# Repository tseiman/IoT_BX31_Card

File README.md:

# IoT BX31 Card

IoT card for Sierra Wireless MangOH (https://mangoh.io) boards.
Connects the Sierra Wirelss  BX3105 Module via UART to the (WP) Module.
The IoT card is easy to use by using the Legato (https://legato.io) AT command interpreter.

## Programming the EEPROM
After hardware production the EEPROM needs to be one time flashed with the Identity and configuration data of the IoT card.
Please see the eeprom folder for further information. 

## Basic testing on MangOH
Ensure that the UART of the WP module is configured correctly to handle the IoT module - e.g. by configuring it via `AT!MAPUART=17,1` command on the WP module (please cross check the WP AT User guide).
**Ensure that the GPIO's are set correctly**. On MangOH red this are GPIO 42 for Firmware update and GPIO 2 for enable. The BX31 IoT module supports update of the Firmware over UART by pulling GPIO 42 low (it is a Active Low Pin on BX3105). For normal operation **pull GPIO42 high (important)**. To reset the card you need to pull "enable" GPIO 2  High and then pull it down again - so the BX3105 gets enabled.

Disable Firmware update GPIO from command line:
```
~# echo 42 >/sys/class/gpio/export
~# echo out >/sys/class/gpio/gpio42/direction
~# echo 0 > /sys/class/gpio/gpio42/value
```
Reset the Module:
```
~# echo 2 >/sys/class/gpio/export
~# echo out >/sys/class/gpio/gpio2/direction
~# echo 1 > /sys/class/gpio/gpio2/value
~# echo 0 > /sys/class/gpio/gpio2/value
```

Now you can connect to the UART by using microcom and it should react to BX31 AT commands:
```
~# microcom -X -s 115200 /dev/ttyHS0
ATI

BX3105

OK
```
You can exit microcom by pressing **CTRL-X**. Please remember that when typing AT commands you'll not see what you type becasue BX31 are not echoing back. 

You can also read the content of the IoT card EEPROM, by reading it over I2C with i2cdump:

```
TBD
```

## Using it the IoT card in Legato

Ensure the UART of the WP module is configured in the right way. On a WP76 this can be done with the `AT!MAPUART=17,1` command. 
For further Information check the AT command guide of the Module you plan to use. 
The IoT module will be then accessible over the `/dev/ttyHS0` UART in Legato.
You might do this setoup out of a Legato application by using the Legato AT interpreter API.

In case you plan to use the BX31 IoT module in an Legato environment and to control it from a Legato Application - ensure that you have read/write access to the device.
This can be configured in the **requires - devices** section of your Legato appliactions **.adef** file - e.g.:

```
requires:
{
    device:
    {
       [rw]    /dev/ttyHS0    /dev/ttyHS0
    }
}

```

Ensure in the same file that you bind the AT Interpreter API to your project:

```
bindings:
{
    bx31_atservice.BX31_ATServiceComponent.le_atClient -> atService.le_atClient
...    
}
```

Now you can use the API to control the BX31 IoT Board - see this snippeds as some example (more glue code might be needed):

```c
        fd = le_tty_Open(BX31_SERIAL_DEVICE, O_RDWR | O_NDELAY | O_NOCTTY | O_NONBLOCK); // opening the UART2 - which is connected to the IoT Board
        if (fd == -1) {
                LE_ERROR("failed to open UART device");
                exit(EXIT_FAILURE);
        }
        
       ...

        LE_ASSERT(le_tty_SetBaudRate(fd, LE_TTY_SPEED_115200) == LE_OK);        // assuming BX31 is on 115200
        LE_ASSERT(le_tty_SetFraming(fd, 'N', 8, 1) == LE_OK);                   // set UART framing to 8bit, No Parity, 1 Stop bit
        LE_ASSERT(le_tty_SetRaw(fd, 10, 30000) == LE_OK);                       // We need raw UART mode (the canonical echo's
                                                                                // back to peer)
       ...

        DevRef = le_atClient_Start(fd);

        cmdRef = le_atClient_Create();                                          // instantiate an AT interpreter client

        /* --- check if we're really talking to BX31 --- */
        LE_INFO("Check BX310x presence");                                       // We ask for device identification string

        LE_ASSERT(le_atClient_SetCommandAndSend
                  (&cmdRef, DevRef, "ATI", "", "OK|ERROR|+CME ERROR",
                   LE_ATDEFS_COMMAND_DEFAULT_TIMEOUT) == LE_OK);

        LE_ASSERT(le_atClient_GetFinalResponse
                  (cmdRef, buffer, LE_ATDEFS_RESPONSE_MAX_BYTES) == LE_OK);

        memset(buffer, 0, 50);

        LE_ASSERT(le_atClient_GetFirstIntermediateResponse
                  (cmdRef, buffer, LE_ATDEFS_RESPONSE_MAX_BYTES) == LE_OK);

        if (strncmp(buffer, "BX310", 4) != 0) {                                 // and compare it with the expected
                LE_ERROR("This doesn seem to be a BX310x bluetooth module, "
                                "exiting. Response was \"%s\"", buffer);        // if the BT module is not answering we better exit

      ...

        LE_INFO("Disable WiFi on BX310x");                                      // here we use the BX just for BT scanning
        LE_ASSERT(le_atClient_SetCommandAndSend
                  (&cmdRef, DevRef, "AT+SRWCFG=0", "", "OK|ERROR|+CME ERROR",
                   LE_ATDEFS_COMMAND_DEFAULT_TIMEOUT) == LE_OK);

``` 

For further information please check the legato AT API https://docs.legato.io/17_09/c_atClient.html
There is also a project related to this IoT Board which is used to do a bluetooth scanning: 
https://github.com/tseiman/SWILegatoBTScanner_BX31_AVS

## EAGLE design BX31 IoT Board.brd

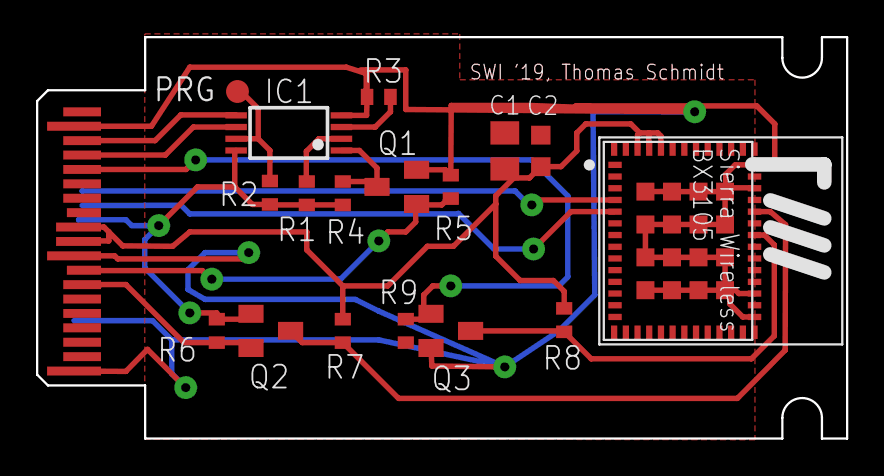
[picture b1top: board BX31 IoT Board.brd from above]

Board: 2 copper layers, 45.0 x 22.3 mm, 18 parts (0 on the bottom side), 16 nets.

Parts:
C1: 22u; C0805K
C2: C0603K
IC1: CAT24C32 YI-GT3; TSSOP8
MODULE1: BX3105
PRG: TPSB1,27; B1,27
Q1, Q2, Q3: BSS138; SOT23
R1, R2, R3, R4, R5, R6, R7, R8, R9: 10k; R0402
U$1: IOT

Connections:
BX-RX_IOT-TX: MODULE1.5, U$1.12
BX-TX_IOT-RX: MODULE1.4, U$1.13
EEPROM_A0: IC1.1, Q1.3, R4.1
EEPROM_A1: IC1.2, R1.1
EEPROM_A2: IC1.3, R3.2
EEPROM_WP: IC1.7, PRG.TP, R2.1
ENABLE: MODULE1.37, Q2.3, R7.1
FW_UPDATE: MODULE1.35, Q3.3, R8.1
GND: C1.2, C2.2, IC1.4, MODULE1.28, MODULE1.30, MODULE1.39, MODULE1.41, MODULE1.G1, MODULE1.G2, MODULE1.G3, MODULE1.G4, MODULE1.G5, MODULE1.G6, MODULE1.G7, MODULE1.G8, MODULE1.G9, MODULE1.G10, MODULE1.G11, MODULE1.G12, MODULE1.G13, MODULE1.G14, MODULE1.G15, MODULE1.G16, Q1.2, Q3.2, R3.1, R5.1, R9.2, U$1.4, U$1.21, U$1.30, U$1.38
GPIO_1_1V8: Q3.1, R9.1, U$1.24
I2C_SCL: IC1.6, U$1.23
I2C_SDA: IC1.5, U$1.22
N_CARD_DETECT: Q1.1, R5.2, U$1.31
N_RESET: Q2.2, R6.1, U$1.32
VCC_1V8: IC1.8, Q2.1, R1.2, R2.2, R4.2, R6.2, U$1.11
VCC_3V3: C1.1, C2.1, MODULE1.50, MODULE1.51, MODULE1.52, R7.2, R8.2, U$1.28, U$1.29

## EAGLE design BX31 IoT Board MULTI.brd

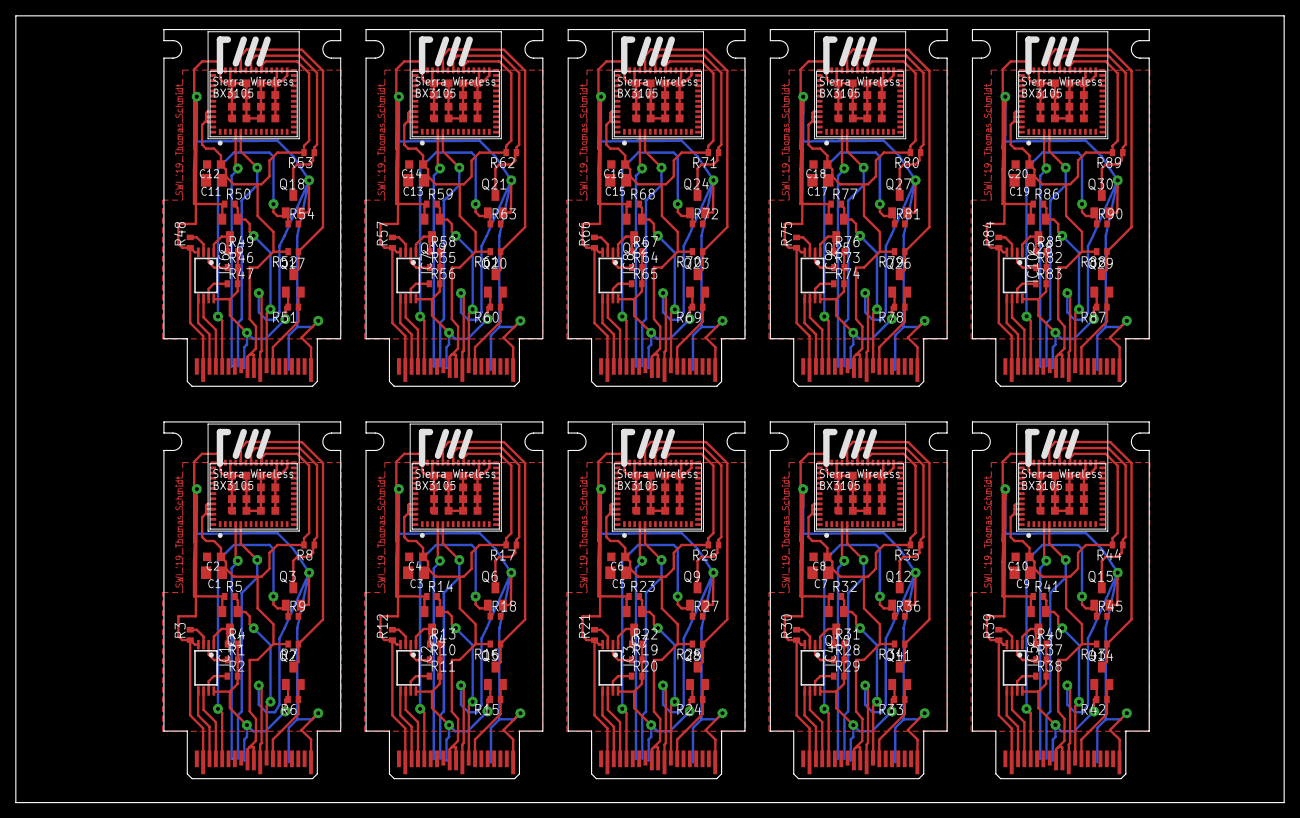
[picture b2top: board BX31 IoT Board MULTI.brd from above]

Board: 2 copper layers, 160.0 x 99.2 mm, 170 parts (0 on the bottom side), 160 nets.

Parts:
C1, C3, C5, C7, C9, C11, C13, C15, C17, C19: 22u; C0805K
C2, C4, C6, C8, C10, C12, C14, C16, C18, C20: C0603K
IC1, IC2, IC3, IC4, IC5, IC6, IC7, IC8, IC9, IC10: CAT24C32 YI-GT3; TSSOP8
MODULE1, MODULE2, MODULE3, MODULE4, MODULE5, MODULE6, MODULE7, MODULE8, MODULE9, MODULE10: BX3105
Q1, Q2, Q3, Q4, Q5, Q6, Q7, Q8, Q9, Q10, Q11, Q12, Q13, Q14, Q15, Q16, Q17, Q18, Q19, Q20, Q21, Q22, Q23, Q24, Q25, Q26, Q27, Q28, Q29, Q30: BSS138; SOT23
R1, R2, R3, R4, R5, R6, R7, R8, R9, R10, R11, R12, R13, R14, R15, R16, R17, R18, R19, R20, R21, R22, R23, R24, R25, R26, R27, R28, R29, R30, R31, R32, R33, R34, R35, R36, R37, R38, R39, R40, R41, R42, R43, R44, R45, R46, R47, R48, R49, R50, R51, R52, R53, R54, R55, R56, R57, R58, R59, R60, R61, R62, R63, R64, R65, R66, R67, R68, R69, R70, R71, R72, R73, R74, R75, R76, R77, R78, R79, R80, R81, R82, R83, R84, R85, R86, R87, R88, R89, R90: 10k; R0402
U$1, U$2, U$3, U$4, U$5, U$6, U$7, U$8, U$9, U$10: IOT

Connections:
BX-RX_IOT-TX: MODULE1.5, U$1.12
BX-RX_IOT-TX1: MODULE2.5, U$2.12
BX-RX_IOT-TX2: MODULE3.5, U$3.12
BX-RX_IOT-TX3: MODULE4.5, U$4.12
BX-RX_IOT-TX4: MODULE5.5, U$5.12
BX-RX_IOT-TX5: MODULE6.5, U$6.12
BX-RX_IOT-TX6: MODULE7.5, U$7.12
BX-RX_IOT-TX7: MODULE8.5, U$8.12
BX-RX_IOT-TX8: MODULE9.5, U$9.12
BX-RX_IOT-TX9: MODULE10.5, U$10.12
BX-TX_IOT-RX: MODULE1.4, U$1.13
BX-TX_IOT-RX1: MODULE2.4, U$2.13
BX-TX_IOT-RX2: MODULE3.4, U$3.13
BX-TX_IOT-RX3: MODULE4.4, U$4.13
BX-TX_IOT-RX4: MODULE5.4, U$5.13
BX-TX_IOT-RX5: MODULE6.4, U$6.13
BX-TX_IOT-RX6: MODULE7.4, U$7.13
BX-TX_IOT-RX7: MODULE8.4, U$8.13
BX-TX_IOT-RX8: MODULE9.4, U$9.13
BX-TX_IOT-RX9: MODULE10.4, U$10.13
EEPROM_A0: IC1.1, Q1.3, R4.1
EEPROM_A1: IC1.2, R1.1
EEPROM_A2: IC1.3, R3.2
EEPROM_A3: IC2.3, R12.2
EEPROM_A4: IC2.2, R10.1
EEPROM_A5: IC2.1, Q4.3, R13.1
EEPROM_A6: IC3.3, R21.2
EEPROM_A7: IC3.2, R19.1
EEPROM_A8: IC3.1, Q7.3, R22.1
EEPROM_A9: IC4.3, R30.2
EEPROM_A10: IC4.2, R28.1
EEPROM_A11: IC4.1, Q10.3, R31.1
EEPROM_A12: IC5.3, R39.2
EEPROM_A13: IC5.2, R37.1
EEPROM_A14: IC5.1, Q13.3, R40.1
EEPROM_A15: IC6.3, R48.2
EEPROM_A16: IC6.2, R46.1
EEPROM_A17: IC6.1, Q16.3, R49.1
EEPROM_A18: IC7.3, R57.2
EEPROM_A19: IC7.2, R55.1
EEPROM_A20: IC7.1, Q19.3, R58.1
EEPROM_A21: IC8.3, R66.2
EEPROM_A22: IC8.2, R64.1
EEPROM_A23: IC8.1, Q22.3, R67.1
EEPROM_A24: IC9.3, R75.2
EEPROM_A25: IC9.2, R73.1
EEPROM_A26: IC9.1, Q25.3, R76.1
EEPROM_A27: IC10.3, R84.2
EEPROM_A28: IC10.2, R82.1
EEPROM_A29: IC10.1, Q28.3, R85.1
EEPROM_WP: IC1.7, R2.1
EEPROM_WP1: IC2.7, R11.1
EEPROM_WP2: IC3.7, R20.1
EEPROM_WP3: IC4.7, R29.1
EEPROM_WP4: IC5.7, R38.1
EEPROM_WP5: IC6.7, R47.1
EEPROM_WP6: IC7.7, R56.1
EEPROM_WP7: IC8.7, R65.1
EEPROM_WP8: IC9.7, R74.1
EEPROM_WP9: IC10.7, R83.1
ENABLE: MODULE1.37, Q2.3, R7.1
ENABLE1: MODULE2.37, Q5.3, R16.1
ENABLE2: MODULE3.37, Q8.3, R25.1
ENABLE3: MODULE4.37, Q11.3, R34.1
ENABLE4: MODULE5.37, Q14.3, R43.1
ENABLE5: MODULE6.37, Q17.3, R52.1
ENABLE6: MODULE7.37, Q20.3, R61.1
ENABLE7: MODULE8.37, Q23.3, R70.1
ENABLE8: MODULE9.37, Q26.3, R79.1
ENABLE9: MODULE10.37, Q29.3, R88.1
FW_UPDATE: MODULE1.35, Q3.3, R8.1
FW_UPDATE1: MODULE2.35, Q6.3, R17.1
FW_UPDATE2: MODULE3.35, Q9.3, R26.1
FW_UPDATE3: MODULE4.35, Q12.3, R35.1
FW_UPDATE4: MODULE5.35, Q15.3, R44.1
FW_UPDATE5: MODULE6.35, Q18.3, R53.1
FW_UPDATE6: MODULE7.35, Q21.3, R62.1
FW_UPDATE7: MODULE8.35, Q24.3, R71.1
FW_UPDATE8: MODULE9.35, Q27.3, R80.1
FW_UPDATE9: MODULE10.35, Q30.3, R89.1
GND: C1.2, C2.2, IC1.4, MODULE1.28, MODULE1.30, MODULE1.39, MODULE1.41, MODULE1.G1, MODULE1.G2, MODULE1.G3, MODULE1.G4, MODULE1.G5, MODULE1.G6, MODULE1.G7, MODULE1.G8, MODULE1.G9, MODULE1.G10, MODULE1.G11, MODULE1.G12, MODULE1.G13, MODULE1.G14, MODULE1.G15, MODULE1.G16, Q1.2, Q3.2, R3.1, R5.1, R9.2, U$1.4, U$1.21, U$1.30, U$1.38
GND1: C3.2, C4.2, IC2.4, MODULE2.28, MODULE2.30, MODULE2.39, MODULE2.41, MODULE2.G1, MODULE2.G2, MODULE2.G3, MODULE2.G4, MODULE2.G5, MODULE2.G6, MODULE2.G7, MODULE2.G8, MODULE2.G9, MODULE2.G10, MODULE2.G11, MODULE2.G12, MODULE2.G13, MODULE2.G14, MODULE2.G15, MODULE2.G16, Q4.2, Q6.2, R12.1, R14.1, R18.2, U$2.4, U$2.21, U$2.30, U$2.38
GND2: C5.2, C6.2, IC3.4, MODULE3.28, MODULE3.30, MODULE3.39, MODULE3.41, MODULE3.G1, MODULE3.G2, MODULE3.G3, MODULE3.G4, MODULE3.G5, MODULE3.G6, MODULE3.G7, MODULE3.G8, MODULE3.G9, MODULE3.G10, MODULE3.G11, MODULE3.G12, MODULE3.G13, MODULE3.G14, MODULE3.G15, MODULE3.G16, Q7.2, Q9.2, R21.1, R23.1, R27.2, U$3.4, U$3.21, U$3.30, U$3.38
GND3: C7.2, C8.2, IC4.4, MODULE4.28, MODULE4.30, MODULE4.39, MODULE4.41, MODULE4.G1, MODULE4.G2, MODULE4.G3, MODULE4.G4, MODULE4.G5, MODULE4.G6, MODULE4.G7, MODULE4.G8, MODULE4.G9, MODULE4.G10, MODULE4.G11, MODULE4.G12, MODULE4.G13, MODULE4.G14, MODULE4.G15, MODULE4.G16, Q10.2, Q12.2, R30.1, R32.1, R36.2, U$4.4, U$4.21, U$4.30, U$4.38
GND4: C9.2, C10.2, IC5.4, MODULE5.28, MODULE5.30, MODULE5.39, MODULE5.41, MODULE5.G1, MODULE5.G2, MODULE5.G3, MODULE5.G4, MODULE5.G5, MODULE5.G6, MODULE5.G7, MODULE5.G8, MODULE5.G9, MODULE5.G10, MODULE5.G11, MODULE5.G12, MODULE5.G13, MODULE5.G14, MODULE5.G15, MODULE5.G16, Q13.2, Q15.2, R39.1, R41.1, R45.2, U$5.4, U$5.21, U$5.30, U$5.38
GND5: C11.2, C12.2, IC6.4, MODULE6.28, MODULE6.30, MODULE6.39, MODULE6.41, MODULE6.G1, MODULE6.G2, MODULE6.G3, MODULE6.G4, MODULE6.G5, MODULE6.G6, MODULE6.G7, MODULE6.G8, MODULE6.G9, MODULE6.G10, MODULE6.G11, MODULE6.G12, MODULE6.G13, MODULE6.G14, MODULE6.G15, MODULE6.G16, Q16.2, Q18.2, R48.1, R50.1, R54.2, U$6.4, U$6.21, U$6.30, U$6.38
GND6: C13.2, C14.2, IC7.4, MODULE7.28, MODULE7.30, MODULE7.39, MODULE7.41, MODULE7.G1, MODULE7.G2, MODULE7.G3, MODULE7.G4, MODULE7.G5, MODULE7.G6, MODULE7.G7, MODULE7.G8, MODULE7.G9, MODULE7.G10, MODULE7.G11, MODULE7.G12, MODULE7.G13, MODULE7.G14, MODULE7.G15, MODULE7.G16, Q19.2, Q21.2, R57.1, R59.1, R63.2, U$7.4, U$7.21, U$7.30, U$7.38
GND7: C15.2, C16.2, IC8.4, MODULE8.28, MODULE8.30, MODULE8.39, MODULE8.41, MODULE8.G1, MODULE8.G2, MODULE8.G3, MODULE8.G4, MODULE8.G5, MODULE8.G6, MODULE8.G7, MODULE8.G8, MODULE8.G9, MODULE8.G10, MODULE8.G11, MODULE8.G12, MODULE8.G13, MODULE8.G14, MODULE8.G15, MODULE8.G16, Q22.2, Q24.2, R66.1, R68.1, R72.2, U$8.4, U$8.21, U$8.30, U$8.38
GND8: C17.2, C18.2, IC9.4, MODULE9.28, MODULE9.30, MODULE9.39, MODULE9.41, MODULE9.G1, MODULE9.G2, MODULE9.G3, MODULE9.G4, MODULE9.G5, MODULE9.G6, MODULE9.G7, MODULE9.G8, MODULE9.G9, MODULE9.G10, MODULE9.G11, MODULE9.G12, MODULE9.G13, MODULE9.G14, MODULE9.G15, MODULE9.G16, Q25.2, Q27.2, R75.1, R77.1, R81.2, U$9.4, U$9.21, U$9.30, U$9.38
GND9: C19.2, C20.2, IC10.4, MODULE10.28, MODULE10.30, MODULE10.39, MODULE10.41, MODULE10.G1, MODULE10.G2, MODULE10.G3, MODULE10.G4, MODULE10.G5, MODULE10.G6, MODULE10.G7, MODULE10.G8, MODULE10.G9, MODULE10.G10, MODULE10.G11, MODULE10.G12, MODULE10.G13, MODULE10.G14, MODULE10.G15, MODULE10.G16, Q28.2, Q30.2, R84.1, R86.1, R90.2, U$10.4, U$10.21, U$10.30, U$10.38
GPIO_1_1V1: Q6.1, R18.1, U$2.24
GPIO_1_1V2: Q9.1, R27.1, U$3.24
GPIO_1_1V3: Q12.1, R36.1, U$4.24
GPIO_1_1V4: Q15.1, R45.1, U$5.24
GPIO_1_1V5: Q18.1, R54.1, U$6.24
GPIO_1_1V6: Q21.1, R63.1, U$7.24
GPIO_1_1V7: Q24.1, R72.1, U$8.24
GPIO_1_1V8: Q3.1, R9.1, U$1.24
GPIO_1_1V9: Q27.1, R81.1, U$9.24
GPIO_1_1V10: Q30.1, R90.1, U$10.24
I2C_SCL: IC1.6, U$1.23
I2C_SCL1: IC2.6, U$2.23
I2C_SCL2: IC3.6, U$3.23
I2C_SCL3: IC4.6, U$4.23
I2C_SCL4: IC5.6, U$5.23
I2C_SCL5: IC6.6, U$6.23
I2C_SCL6: IC7.6, U$7.23
I2C_SCL7: IC8.6, U$8.23
I2C_SCL8: IC9.6, U$9.23
I2C_SCL9: IC10.6, U$10.23
I2C_SDA: IC1.5, U$1.22
I2C_SDA1: IC2.5, U$2.22
I2C_SDA2: IC3.5, U$3.22
I2C_SDA3: IC4.5, U$4.22
I2C_SDA4: IC5.5, U$5.22
I2C_SDA5: IC6.5, U$6.22
I2C_SDA6: IC7.5, U$7.22
I2C_SDA7: IC8.5, U$8.22
I2C_SDA8: IC9.5, U$9.22
I2C_SDA9: IC10.5, U$10.22
N_CARD_DETECT: Q1.1, R5.2, U$1.31
N_CARD_DETECT1: Q4.1, R14.2, U$2.31
N_CARD_DETECT2: Q7.1, R23.2, U$3.31
N_CARD_DETECT3: Q10.1, R32.2, U$4.31
N_CARD_DETECT4: Q13.1, R41.2, U$5.31
N_CARD_DETECT5: Q16.1, R50.2, U$6.31
N_CARD_DETECT6: Q19.1, R59.2, U$7.31
N_CARD_DETECT7: Q22.1, R68.2, U$8.31
N_CARD_DETECT8: Q25.1, R77.2, U$9.31
N_CARD_DETECT9: Q28.1, R86.2, U$10.31
N_RESET: Q2.2, R6.1, U$1.32
N_RESET1: Q5.2, R15.1, U$2.32
N_RESET2: Q8.2, R24.1, U$3.32
N_RESET3: Q11.2, R33.1, U$4.32
N_RESET4: Q14.2, R42.1, U$5.32
N_RESET5: Q17.2, R51.1, U$6.32
N_RESET6: Q20.2, R60.1, U$7.32
N_RESET7: Q23.2, R69.1, U$8.32
N_RESET8: Q26.2, R78.1, U$9.32
N_RESET9: Q29.2, R87.1, U$10.32
VCC_1V1: IC2.8, Q5.1, R10.2, R11.2, R13.2, R15.2, U$2.11
VCC_1V2: IC3.8, Q8.1, R19.2, R20.2, R22.2, R24.2, U$3.11
VCC_1V3: IC4.8, Q11.1, R28.2, R29.2, R31.2, R33.2, U$4.11
VCC_1V4: IC5.8, Q14.1, R37.2, R38.2, R40.2, R42.2, U$5.11
VCC_1V5: IC6.8, Q17.1, R46.2, R47.2, R49.2, R51.2, U$6.11
VCC_1V6: IC7.8, Q20.1, R55.2, R56.2, R58.2, R60.2, U$7.11
VCC_1V7: IC8.8, Q23.1, R64.2, R65.2, R67.2, R69.2, U$8.11
VCC_1V8: IC1.8, Q2.1, R1.2, R2.2, R4.2, R6.2, U$1.11
VCC_1V9: IC9.8, Q26.1, R73.2, R74.2, R76.2, R78.2, U$9.11
VCC_1V10: IC10.8, Q29.1, R82.2, R83.2, R85.2, R87.2, U$10.11
VCC_3V1: C3.1, C4.1, MODULE2.33, MODULE2.50, MODULE2.51, MODULE2.52, R16.2, R17.2, U$2.28, U$2.29
VCC_3V2: C5.1, C6.1, MODULE3.33, MODULE3.50, MODULE3.51, MODULE3.52, R25.2, R26.2, U$3.28, U$3.29
VCC_3V3: C1.1, C2.1, MODULE1.33, MODULE1.50, MODULE1.51, MODULE1.52, R7.2, R8.2, U$1.28, U$1.29
VCC_3V4: C7.1, C8.1, MODULE4.33, MODULE4.50, MODULE4.51, MODULE4.52, R34.2, R35.2, U$4.28, U$4.29
VCC_3V5: C9.1, C10.1, MODULE5.33, MODULE5.50, MODULE5.51, MODULE5.52, R43.2, R44.2, U$5.28, U$5.29
VCC_3V6: C11.1, C12.1, MODULE6.33, MODULE6.50, MODULE6.51, MODULE6.52, R52.2, R53.2, U$6.28, U$6.29
VCC_3V7: C13.1, C14.1, MODULE7.33, MODULE7.50, MODULE7.51, MODULE7.52, R61.2, R62.2, U$7.28, U$7.29
VCC_3V8: C15.1, C16.1, MODULE8.33, MODULE8.50, MODULE8.51, MODULE8.52, R70.2, R71.2, U$8.28, U$8.29
VCC_3V9: C17.1, C18.1, MODULE9.33, MODULE9.50, MODULE9.51, MODULE9.52, R79.2, R80.2, U$9.28, U$9.29
VCC_3V10: C19.1, C20.1, MODULE10.33, MODULE10.50, MODULE10.51, MODULE10.52, R88.2, R89.2, U$10.28, U$10.29

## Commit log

2019-05-06 Delete BX31 IoT Board MULTI_BOTTOM_Copper.pdf
    Delete Multi PDFs
2019-05-06 Delete BX31 IoT Board MULTI_BUTTOM_Stop.pdf
    Delete Multi PDFs
2019-05-06 Delete BX31 IoT Board MULTI_TOP_Copper.pdf
    Delete Multi PDFs
2019-05-06 Delete BX31 IoT Board MULTI_TOP_Stop.pdf
    Delete Multi PDFs
2019-05-06 Delete BX31 IoT Board MULTI.brd
    Delete Multi Board
2019-05-06 removed multi
2019-05-06 removed BX31 Pin 33 supply, added testpoint for EEPROM, fixerd layout
2019-05-06 Delete BX31 IoT Board_SOLDER-CREAM_BOTTOM.pdf
    Remove solder masks
2019-05-06 Delete BX31 IoT Board_SOLDER-CREAM_BOTTOM_NEG.pdf
    Remove solder masks
2019-05-06 Delete BX31 IoT Board_SOLDER-CREAM_TOP.pdf
    Remove solder masks
2019-05-06 Delete BX31 IoT Board_SOLDER-CREAM_TOP_NEG.pdf
    Remove solder masks
2019-05-06 Delete BX31 IoT Board_SOLDER_TOP.pdf
    Remove solder masks
2019-05-06 Delete BX31 IoT Board.s##
    cleanup
2019-05-06 Delete test_export.scr
    clean up
2019-05-06 updated pictures
2019-05-10 Added eeprom programming part and template; Compelted Readme
2019-05-21 Updated README with basic testing
2019-05-21 Updated Readme with basic CLI usage
2019-05-21 small corrections
2019-05-22 minor corrections
2019-11-23 Corrected some minor issue
